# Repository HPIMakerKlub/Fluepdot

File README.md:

# Fluepdot
This is going to be all about controlling Annax 37623 flipdot displays.
More will follow soon.

In case of questions contact us via github.

Maintainer: @fluepke, @kryptokommunist

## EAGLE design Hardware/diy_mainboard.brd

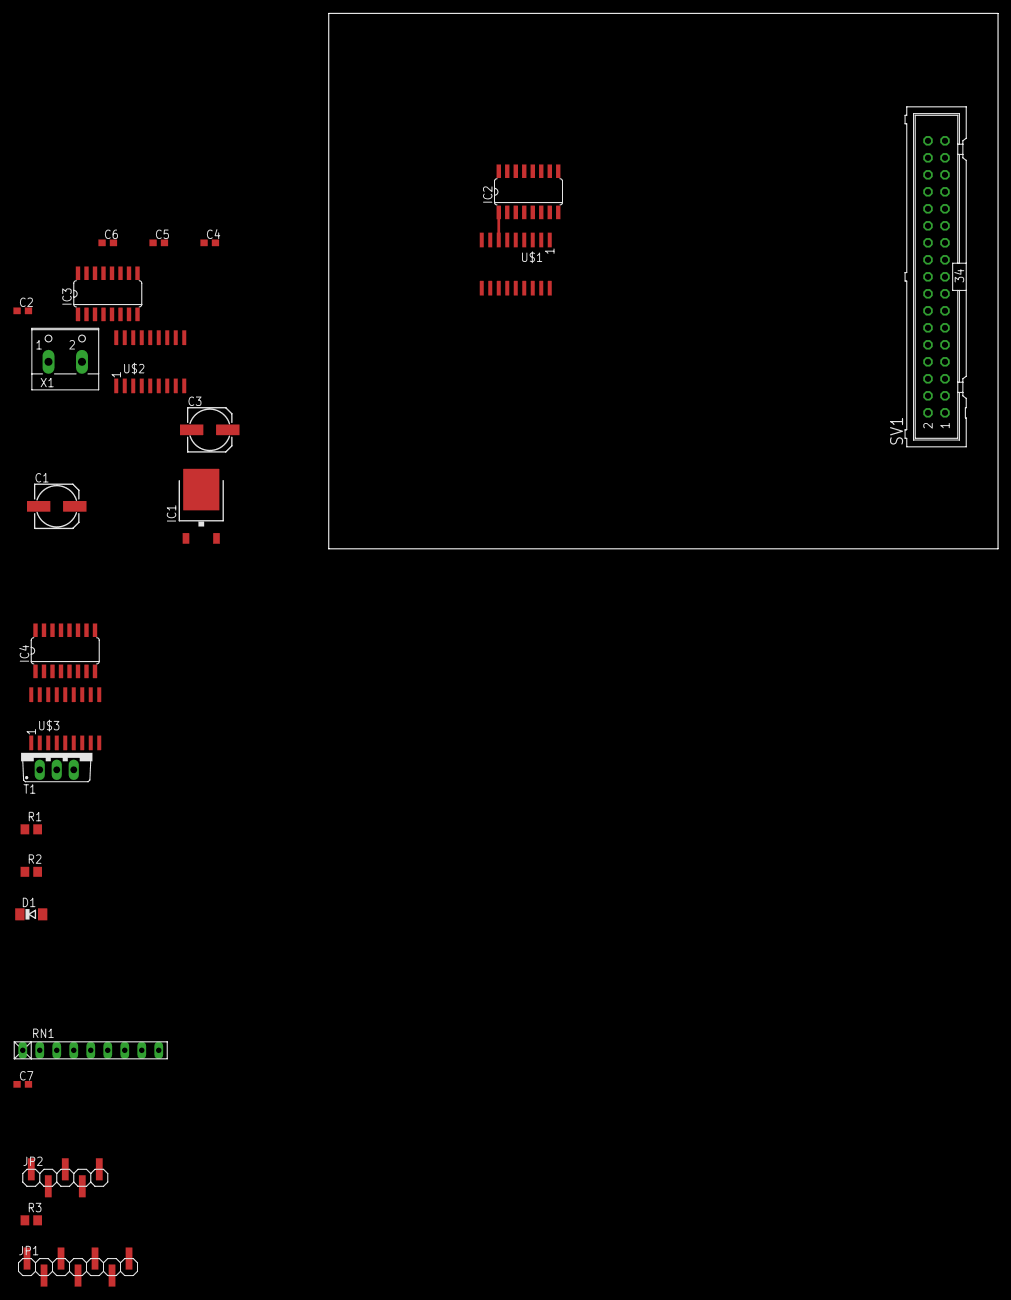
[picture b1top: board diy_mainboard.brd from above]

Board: 2 copper layers, 100.0 x 80.0 mm, 24 parts (0 on the bottom side), 60 nets.

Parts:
C1, C3: 100µF; 153CLV-0605
C2, C4, C5, C6, C7: 100nF; C0603
D1: LL4148; SOD80C
IC1: 7805DT; TO252
IC2, IC3, IC4: 74HC595D; SO16
JP1: 1X07SMD
JP2: 1X05SMD
R1, R3: 1k; R0805
R2: 10k; R0805
RN1: RN-9
SV1: ML34
T1: TIP131; TO220BV
U$1, U$2: TBD62783AFGSO18; TBD62783AFG
U$3: ULN2803; TBD62783AFG
X1: W237-102

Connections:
+5V: C3.+, C4.1, C5.2, C6.2, C7.2, IC1.2, IC2.16, IC3.16, IC4.16, JP1.7
+12V: C1.+, C2.1, D1.C, IC1.1, R2.1, R3.1, RN1.1, SV1.21, SV1.22, SV1.23, SV1.24, SV1.29, U$1.9, U$2.9, X1.1
CLEAR: D1.A, SV1.17, SV1.18, SV1.19, SV1.20, T1.2
CLOCK: R3.2, SV1.34, U$3.17
GND: C1.-, C2.2, C3.-, C4.2, C5.1, C6.1, C7.1, IC1.3, IC2.8, IC3.8, IC4.8, JP1.6, SV1.25, SV1.26, SV1.27, SV1.28, SV1.32, SV1.33, T1.3, U$1.10, U$2.10, U$3.9, X1.2
unnamed: IC2.15, U$1.8
unnamed: IC2.1, U$1.7
unnamed: IC2.2, U$1.6
unnamed: IC2.3, U$1.5
unnamed: IC2.4, U$1.4
unnamed: IC2.5, U$1.3
unnamed: IC2.6, U$1.2
unnamed: IC2.7, U$1.1
unnamed: IC3.15, U$2.1
unnamed: IC3.1, U$2.2
unnamed: IC3.2, U$2.3
unnamed: IC3.3, U$2.4
unnamed: IC3.4, U$2.5
unnamed: IC3.5, U$2.6
unnamed: IC3.6, U$2.7
unnamed: IC3.7, U$2.8
unnamed: IC2.9, IC3.14
unnamed: IC2.11, IC3.11, IC4.11, JP1.4
unnamed: IC2.10, IC3.10, IC4.10, JP1.3
unnamed: IC2.12, IC3.12, IC4.12, JP1.2
unnamed: IC2.13, IC3.13, IC4.13, JP1.1
unnamed: IC3.9, IC4.14
unnamed: IC4.15, U$3.1
unnamed: IC4.1, U$3.2
unnamed: IC4.2, U$3.3
unnamed: IC4.3, U$3.4
unnamed: IC4.4, U$3.5
unnamed: IC4.5, U$3.6
unnamed: IC4.6, U$3.7
unnamed: IC4.7, U$3.8
unnamed: R1.2, T1.1
unnamed: R1.1, R2.2, U$3.18
unnamed: IC2.14, JP1.5
RESET: RN1.3, SV1.31, U$3.16
SELECT1: JP2.1, RN1.4, U$3.15
SELECT2: JP2.2, RN1.5, U$3.14
SELECT3: JP2.3, RN1.6, U$3.13
SELECT4: JP2.4, RN1.7, U$3.11
SELECT5: JP2.5, RN1.8, U$3.12
Y0: SV1.1, U$1.18
Y1: SV1.2, U$1.17
Y2: SV1.3, U$1.16
Y3: SV1.4, U$1.15
Y4: SV1.5, U$1.14
Y5: SV1.6, U$1.13
Y6: SV1.7, U$1.12
Y7: SV1.8, U$1.11
Y8: SV1.9, U$2.18
Y9: SV1.10, U$2.17
Y10: SV1.11, U$2.16
Y11: SV1.12, U$2.15
Y12: SV1.13, U$2.14
Y13: SV1.14, U$2.13
Y14: SV1.15, U$2.12
Y15: SV1.16, U$2.11

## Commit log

2016-12-10 Schematic added.
2016-12-10 Add Arduino lib for flip dot
